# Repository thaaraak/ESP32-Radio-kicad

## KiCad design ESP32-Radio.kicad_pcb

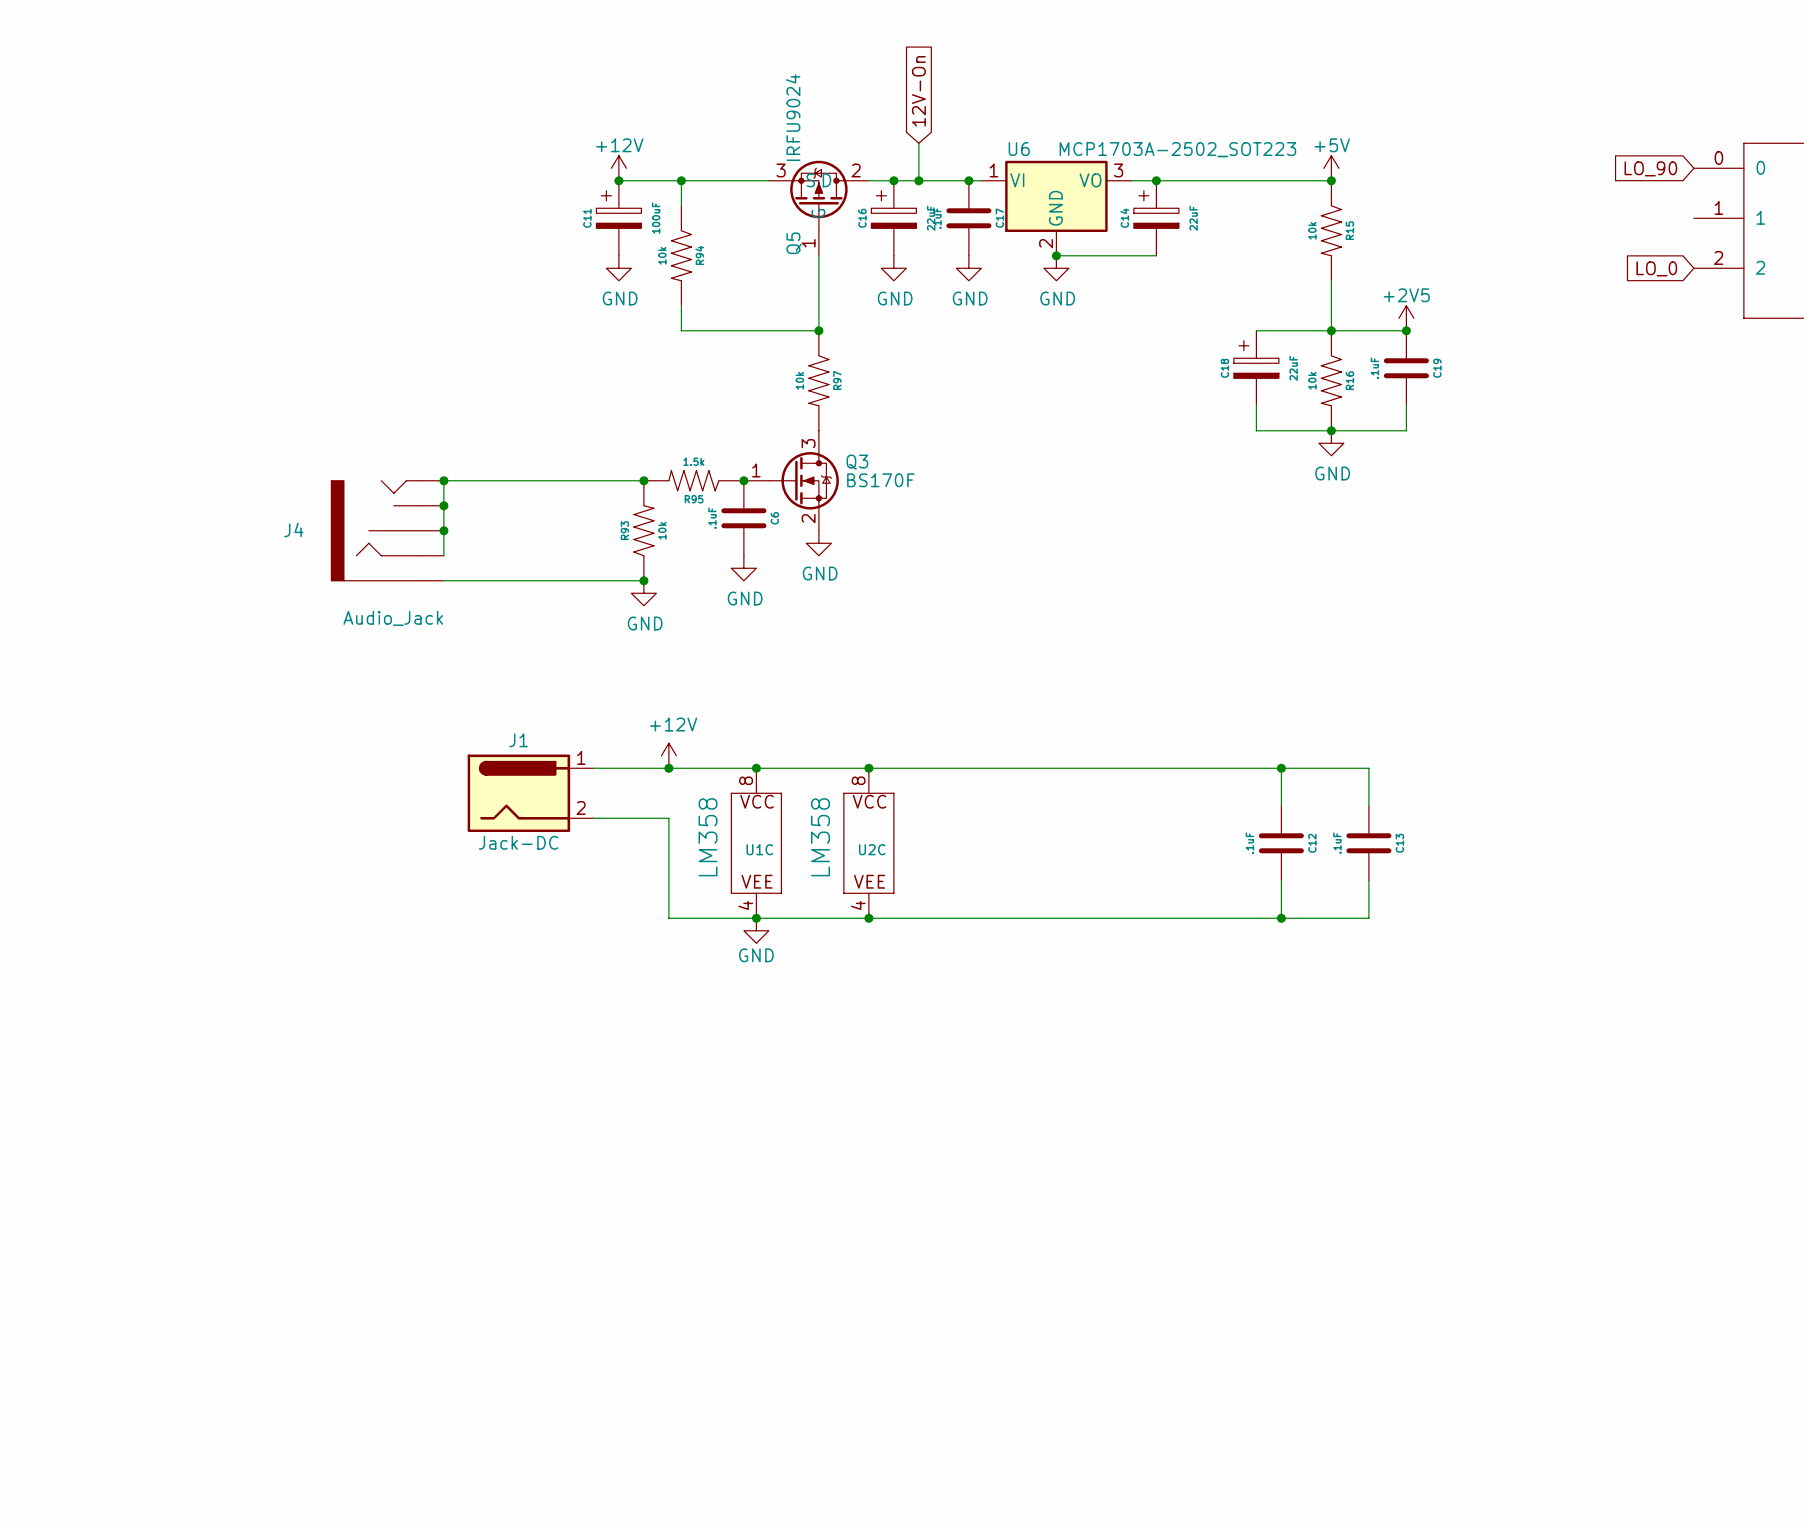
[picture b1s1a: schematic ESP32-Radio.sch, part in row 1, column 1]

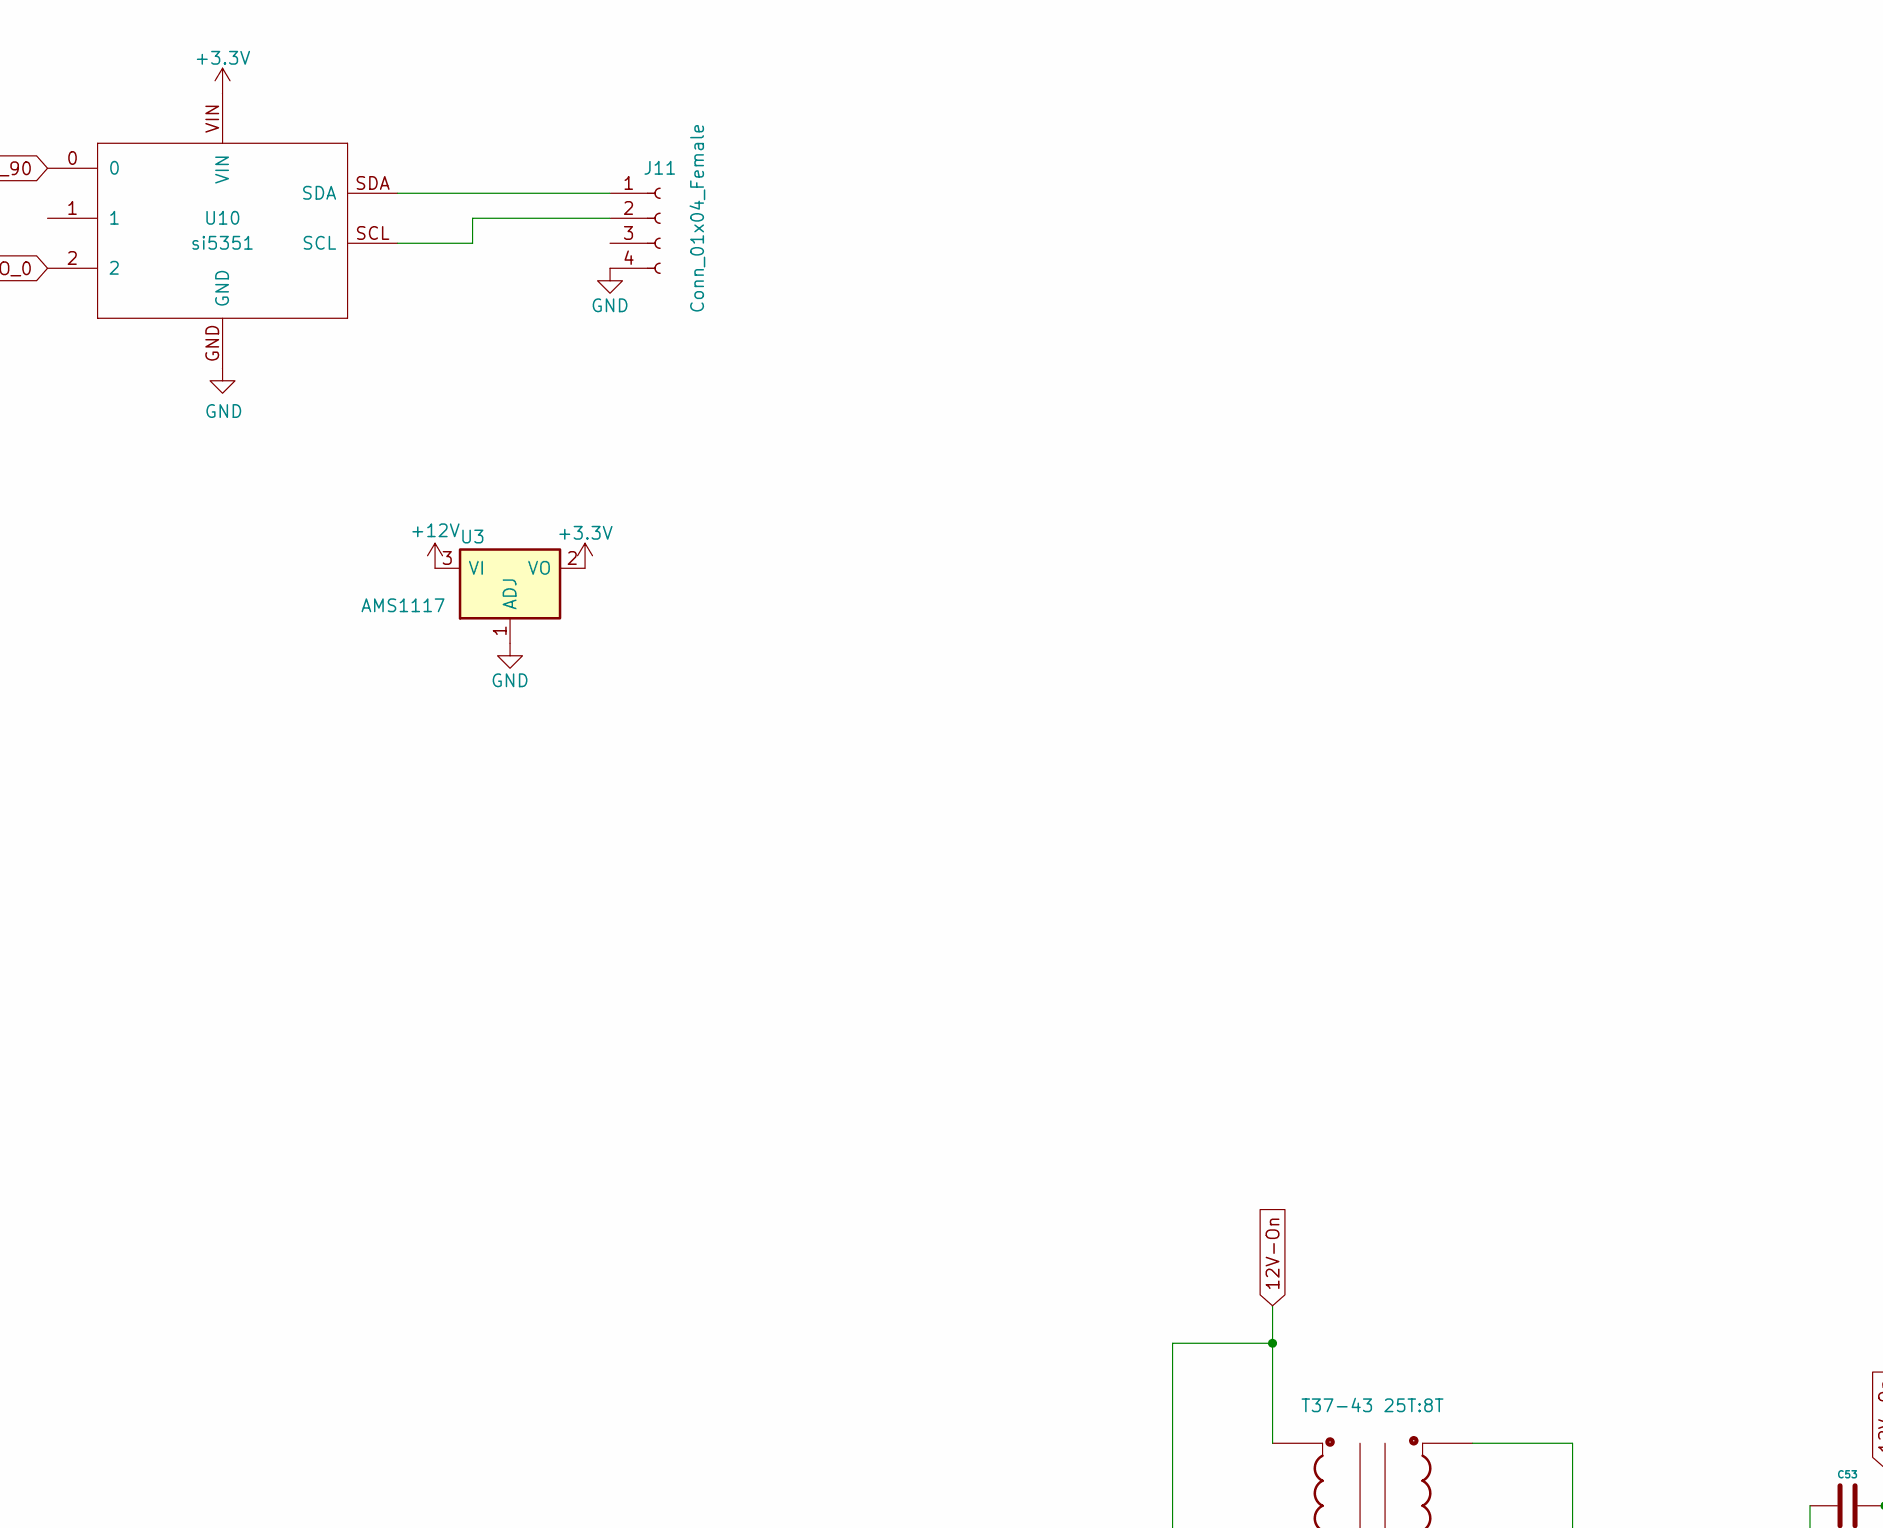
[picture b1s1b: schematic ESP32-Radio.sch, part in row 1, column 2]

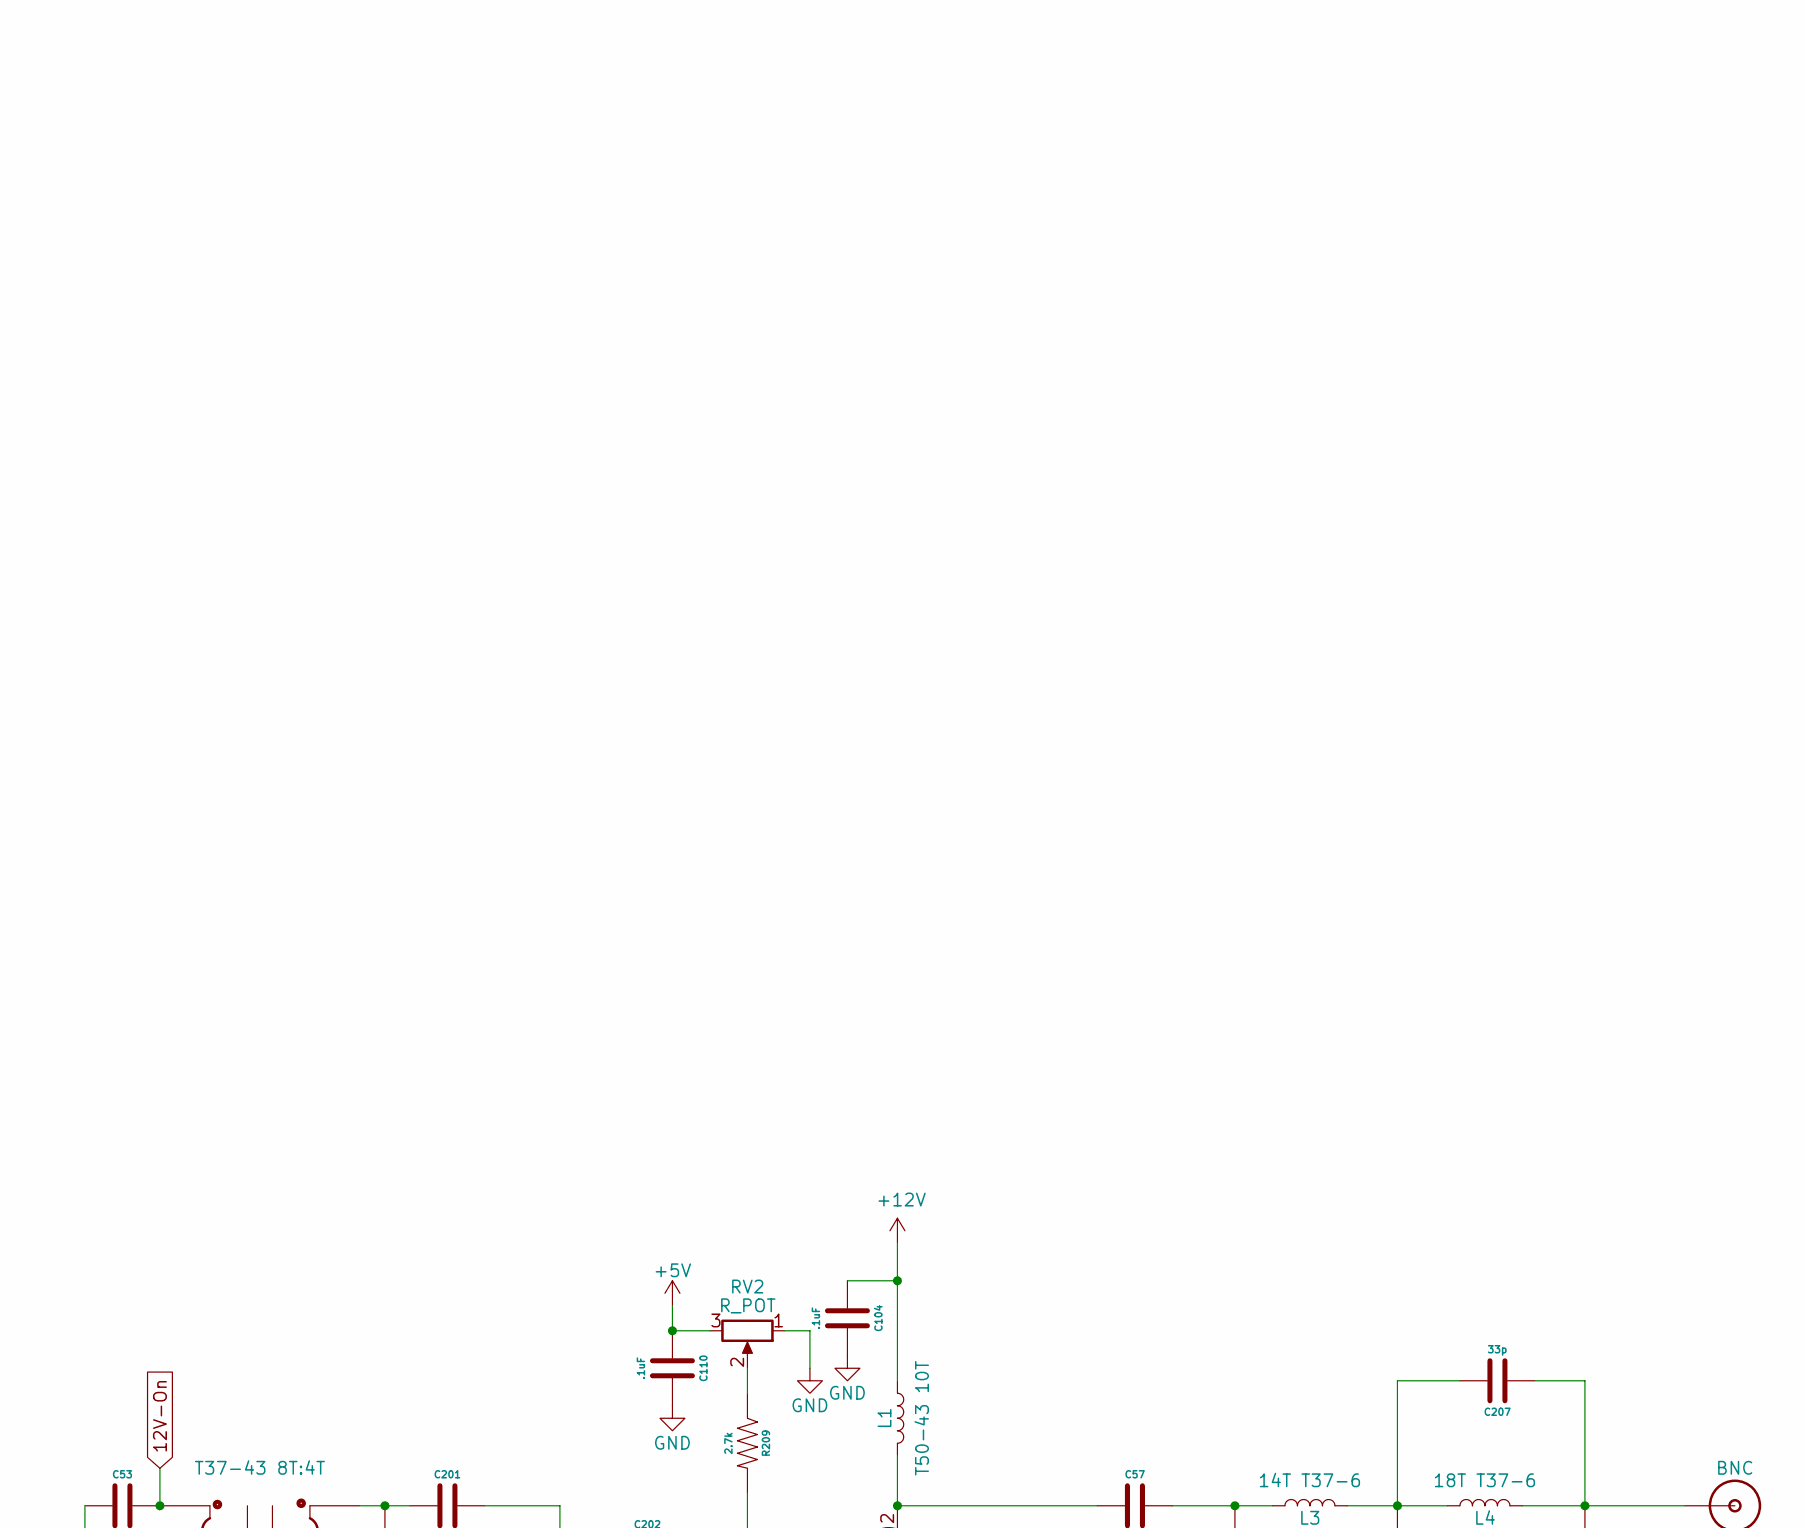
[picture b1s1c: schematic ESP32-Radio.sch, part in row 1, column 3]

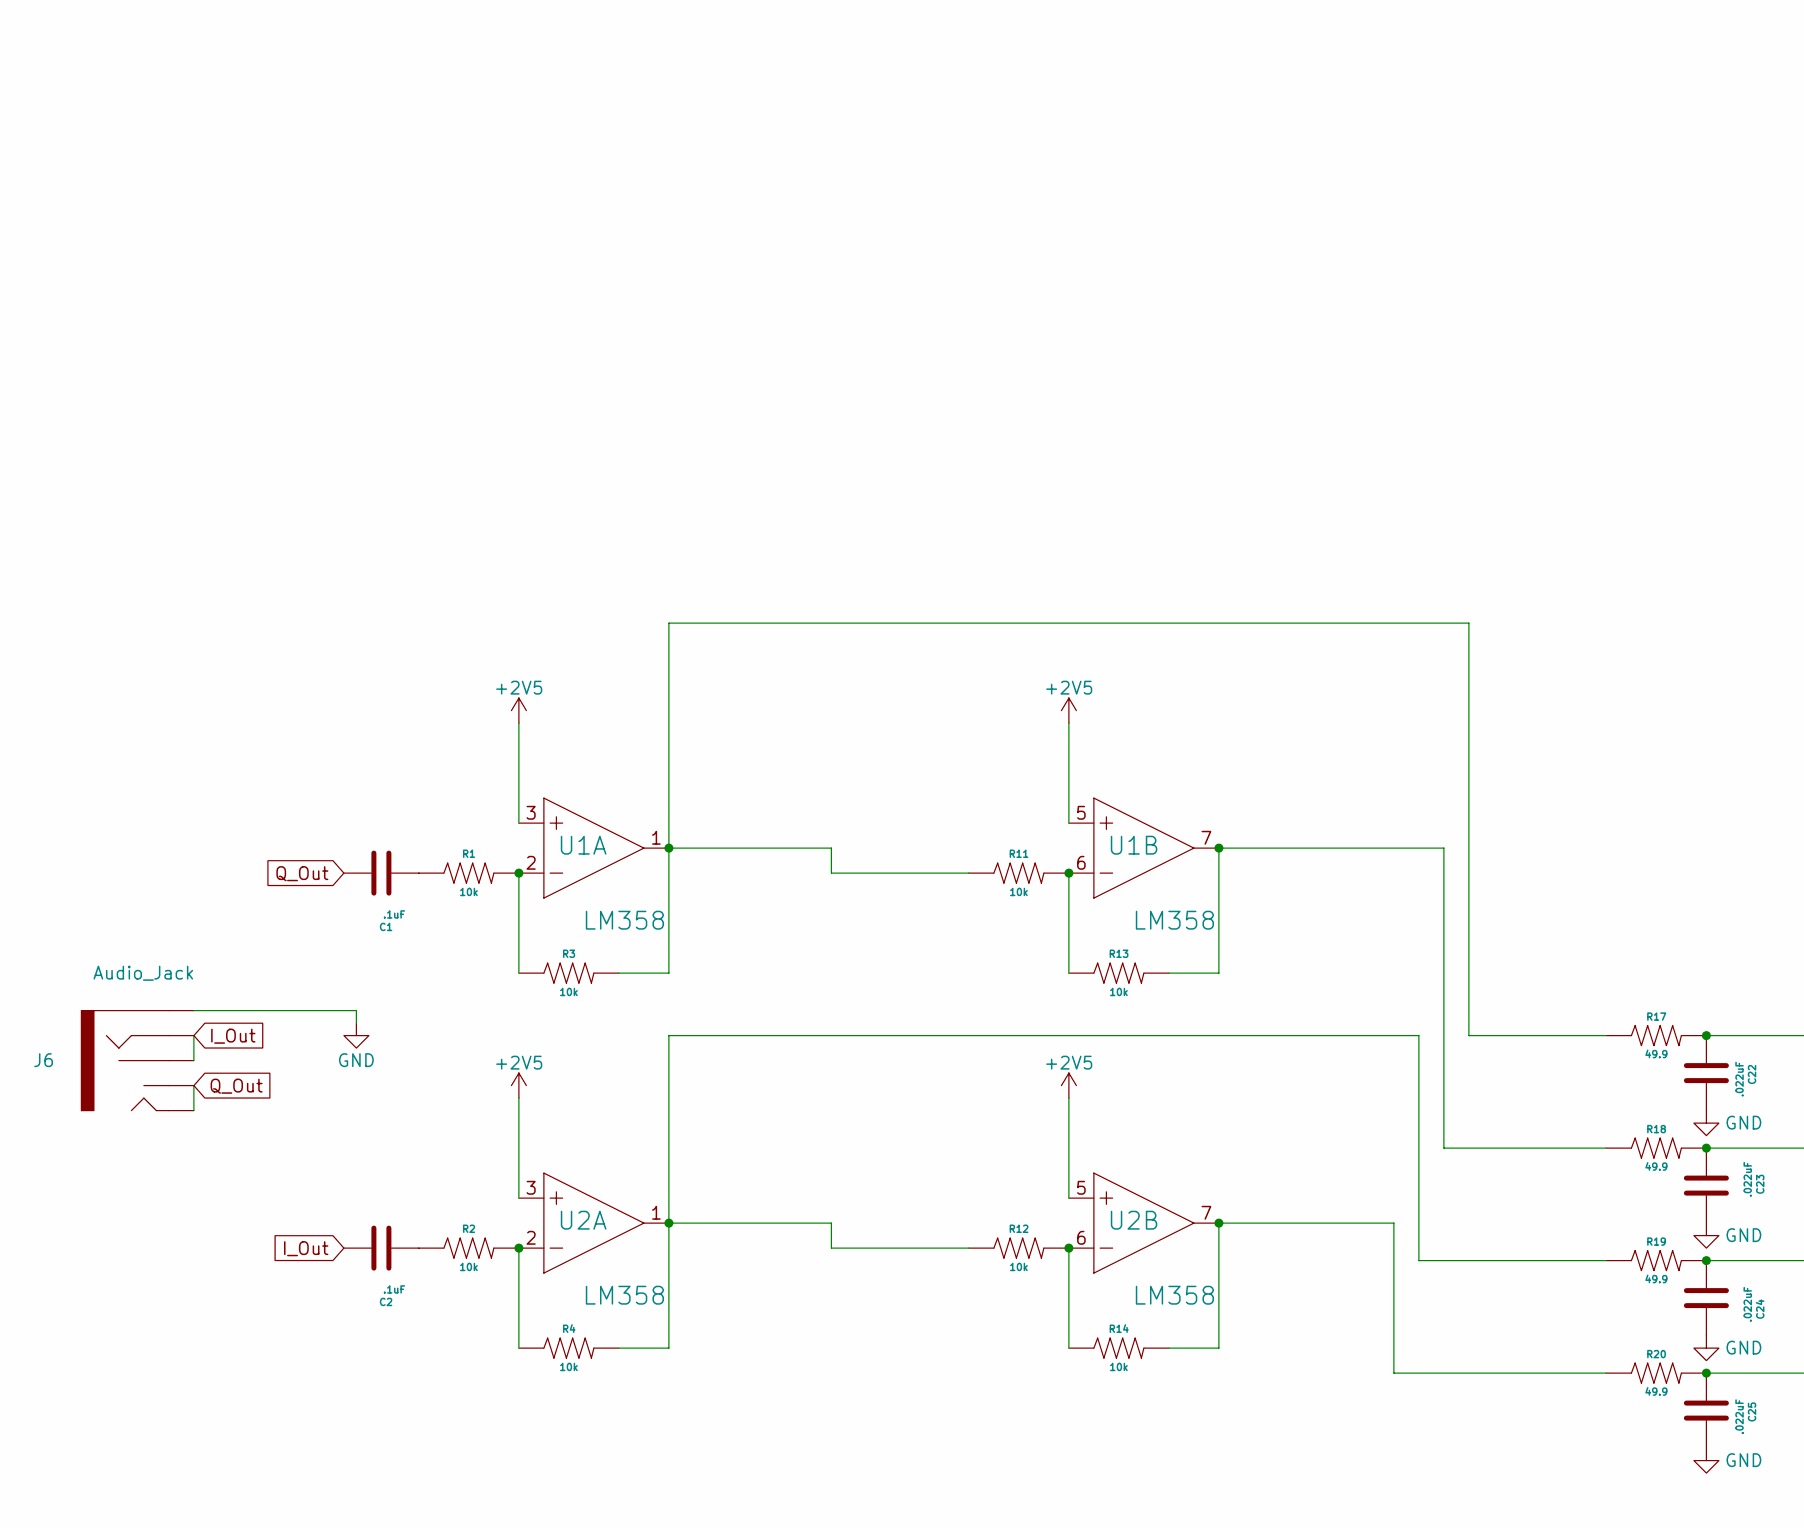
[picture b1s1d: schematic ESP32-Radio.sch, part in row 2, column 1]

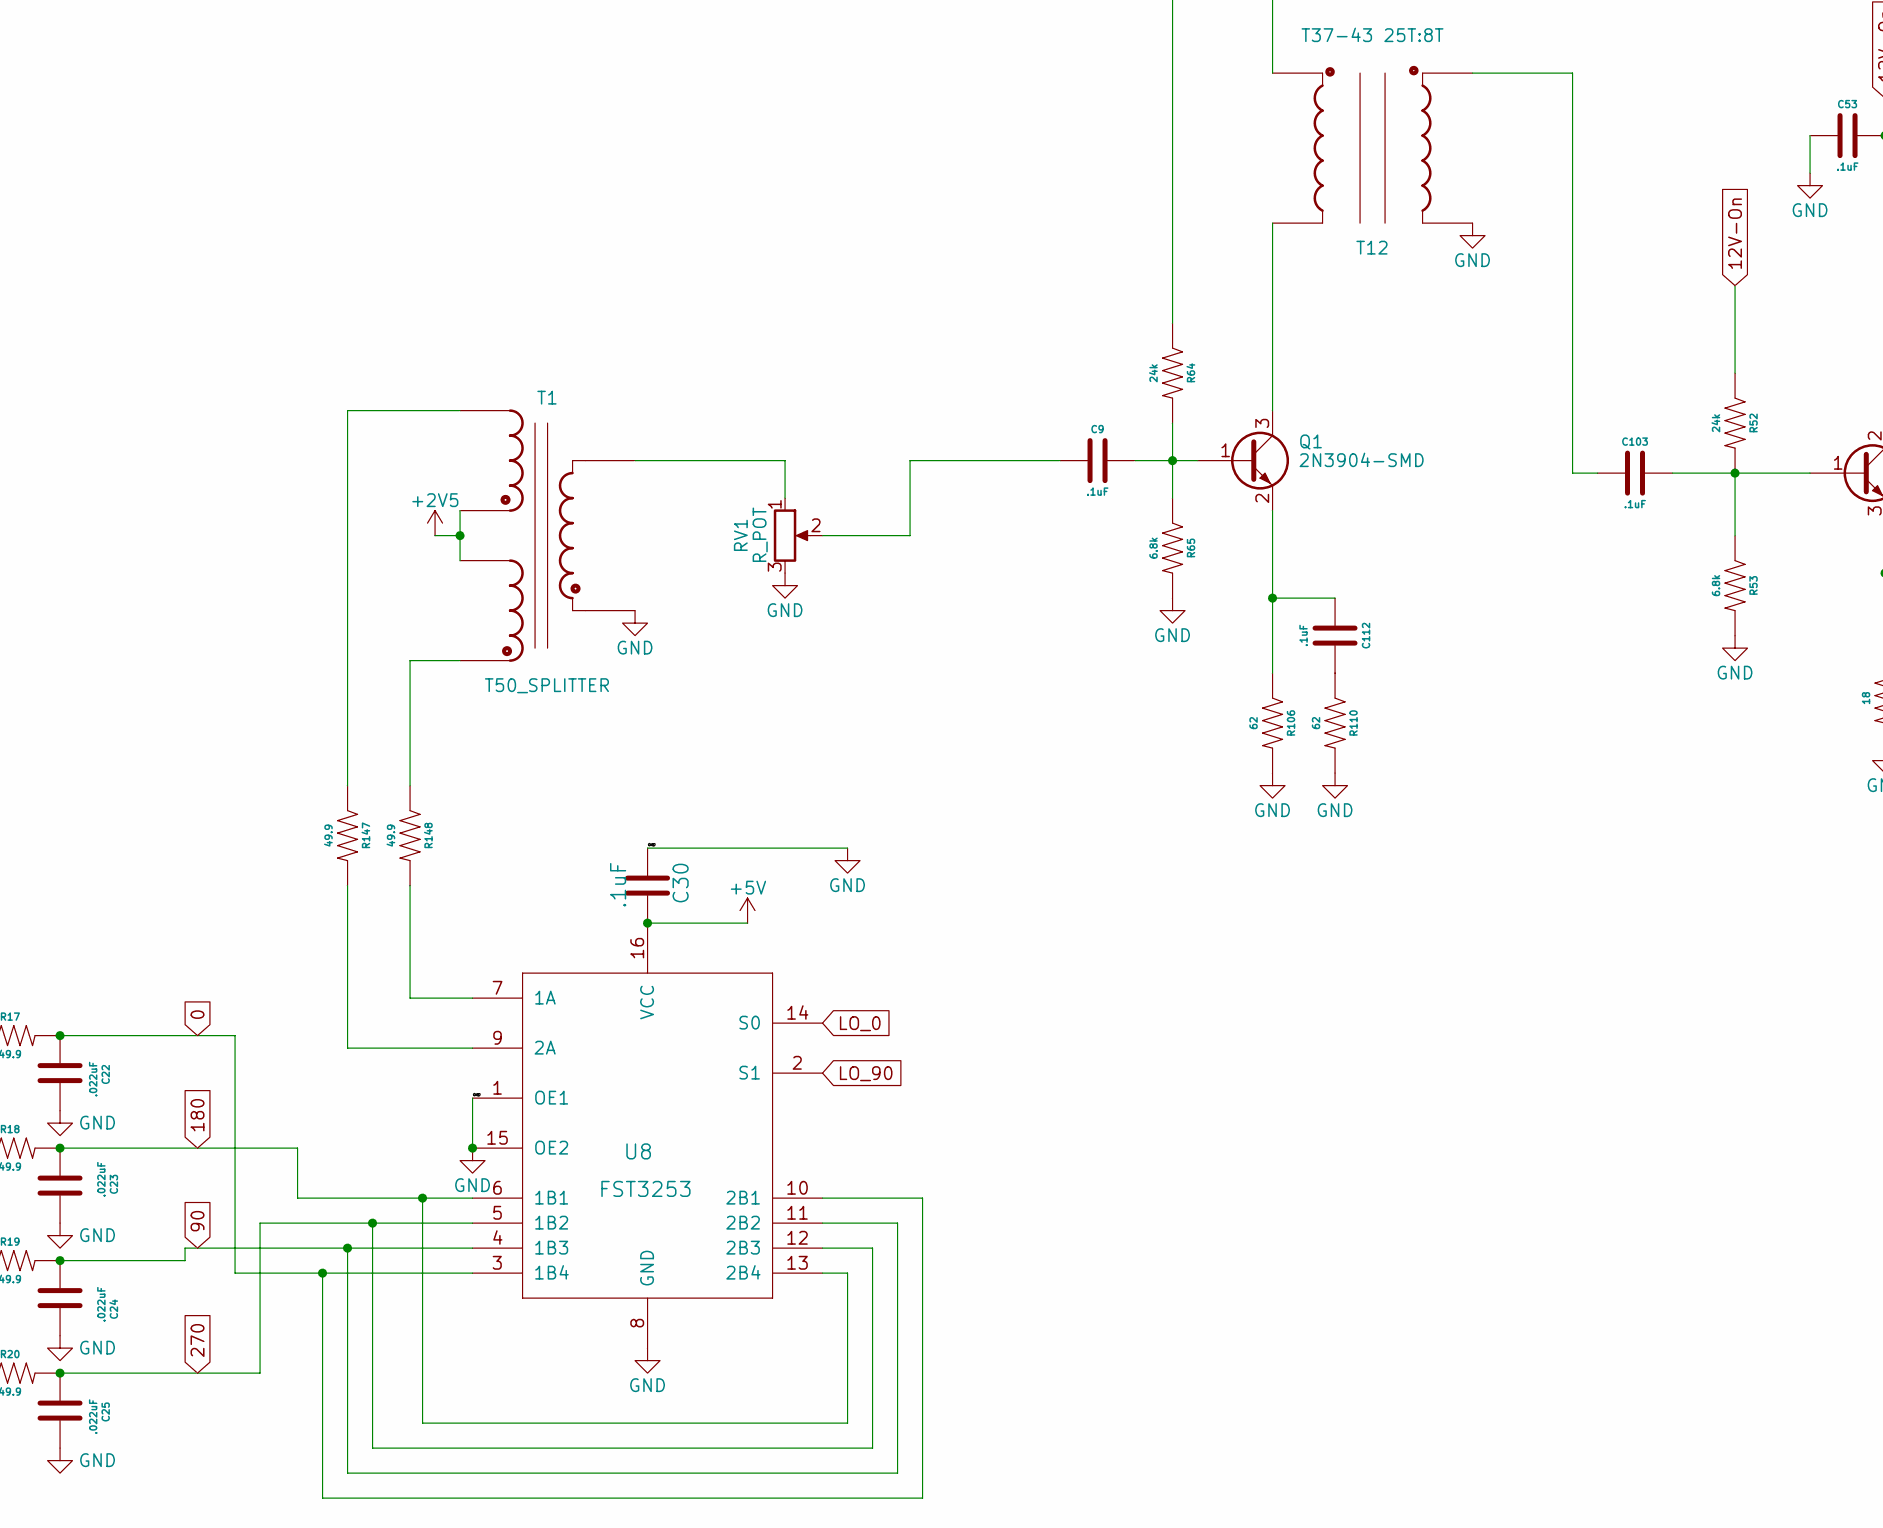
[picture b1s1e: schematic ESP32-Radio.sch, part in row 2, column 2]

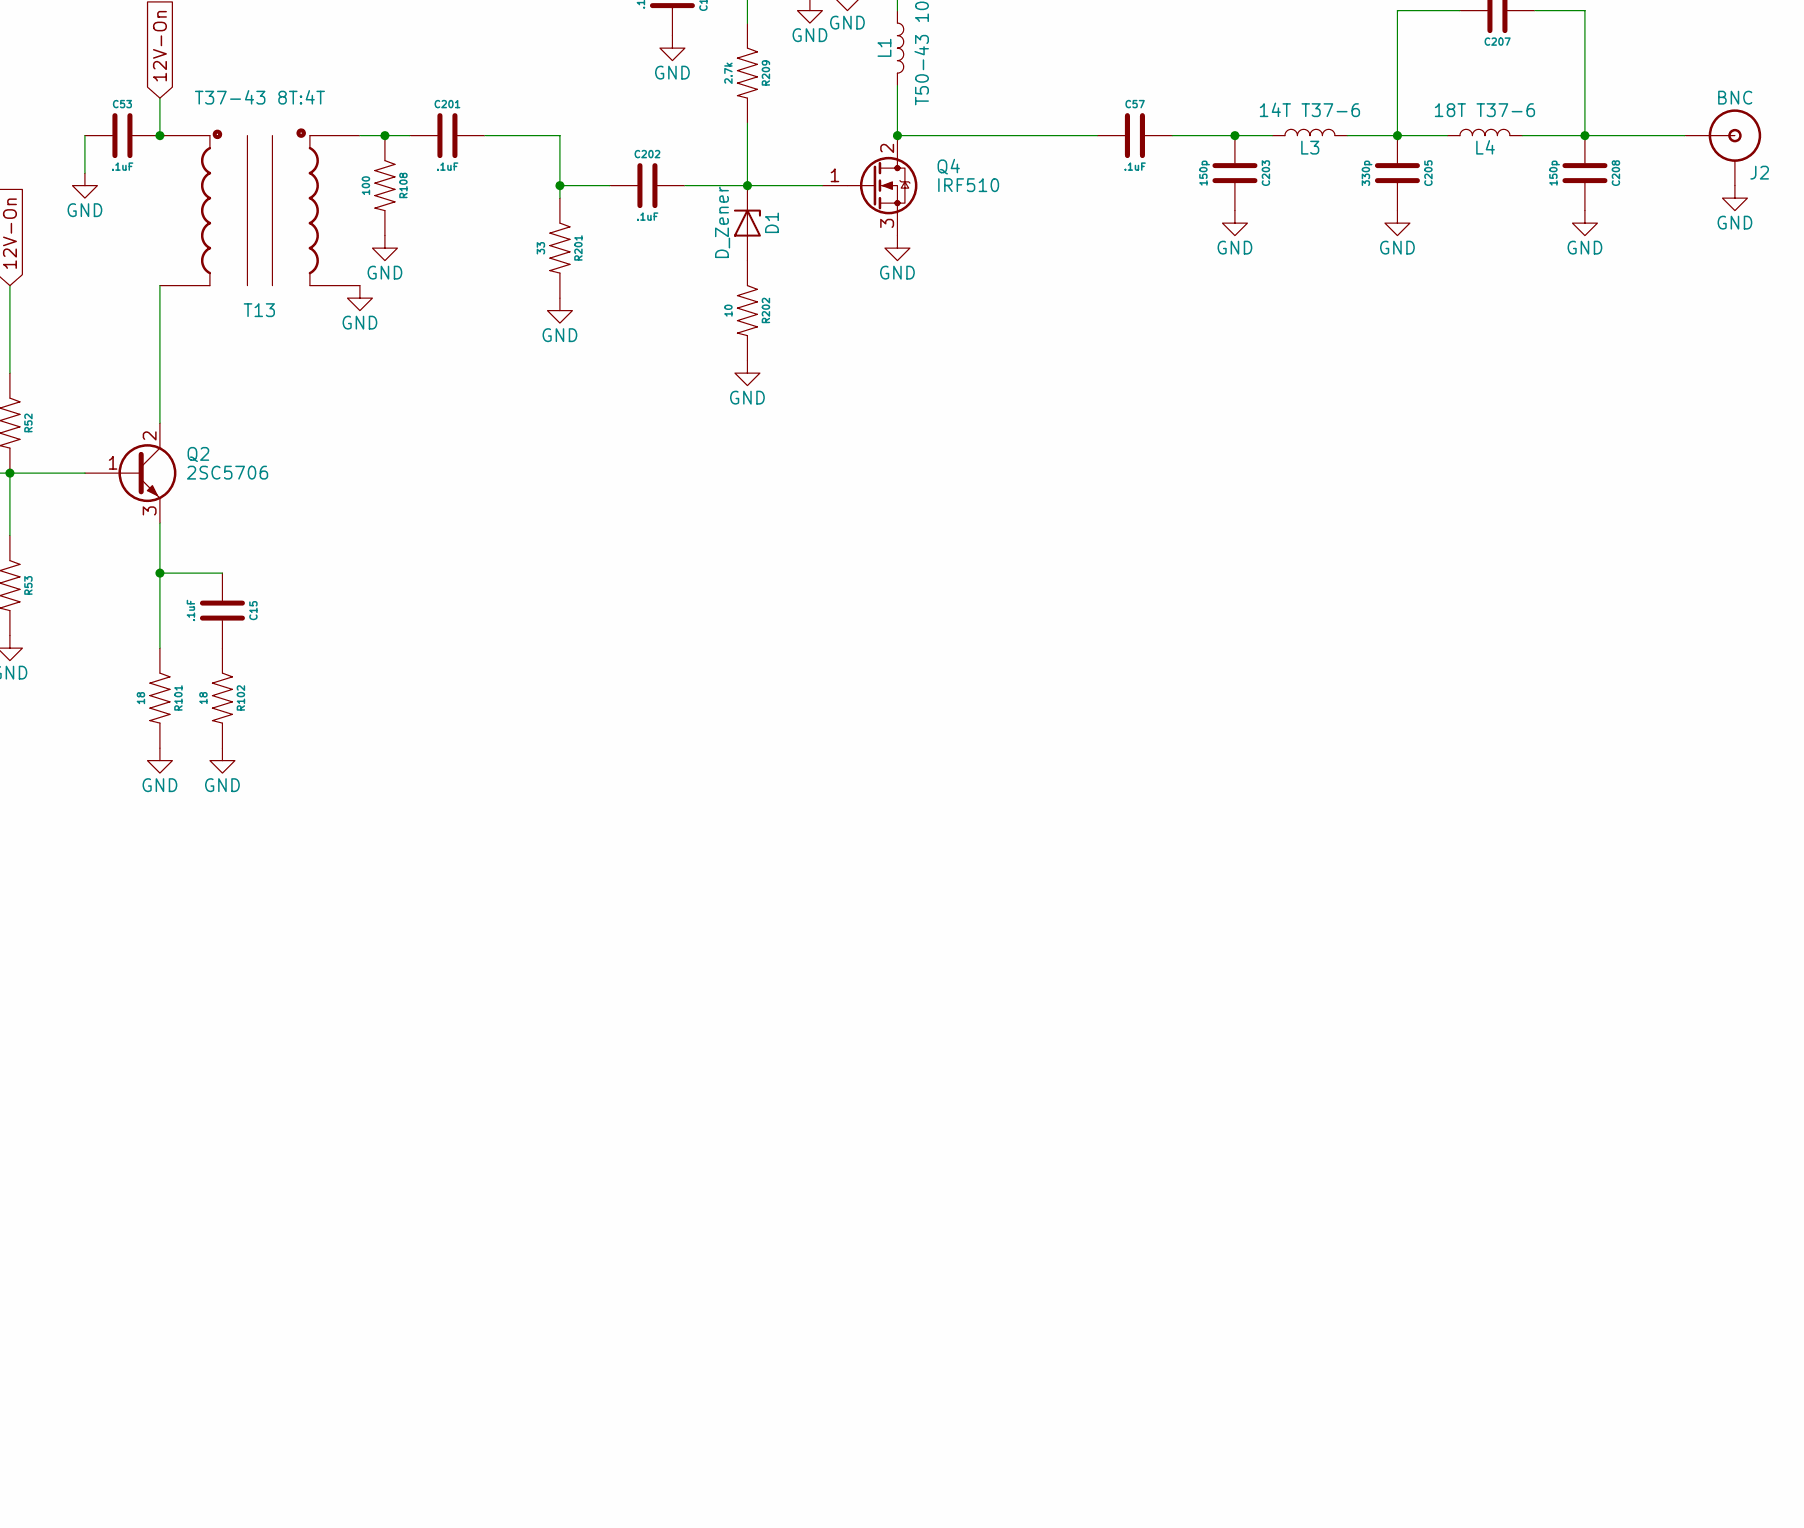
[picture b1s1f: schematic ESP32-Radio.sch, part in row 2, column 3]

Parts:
C1, C2, C6, C9, C12, C13, C15, C17, C19, C30, C53, C57, C103, C104, C110, C112, C201, C202: .1uF; Capacitor 0805
C11: 100uF; Cap_6.3x5.4
C14, C16, C18: 22uF; Cap_4x5.4
C22, C23, C24, C25: .022uF; Capacitor 1206
C203, C208: 150p; Capacitor 1206
C205: 330p; Capacitor 1206
C207: 33p; Capacitor 1206
D1: D_Zener; D_MiniMELF
J1: Jack-DC; BarrelJack_Horizontal
J2: BNC
J4, J6: Audio_Jack
J11: Conn_01x04_Female; PinHeader_1x04_P2.54mm_Vertical
L1: T50-43 10T; T50_Inductor
L3: 14T T37-6; T37_Inductor
L4: 18T T37-6; T37_Inductor
Q1: 2N3904-SMD; SOT-23
Q2: 2SC5706; TO-252-2
Q3: BS170F; SOT-23
Q4: IRF510; TO-220-3_Vertical
Q5: IRFU9024; TO-251-3_Vertical
R1, R2, R3, R4, R11, R12, R13, R14, R15, R16, R93, R94, R97: 10k; Resistor 0805
R17, R18, R19, R20, R147, R148: 49.9; Resistor 0805
R52, R64: 24k; Resistor 0805
R53, R65: 6.8k; Resistor 0805
R95: 1.5k; Resistor 0805
R101, R102: 18; Resistor 0805
R106, R110: 62; Resistor 0805
R108: 100; Resistor 0805
R201: 33; Resistor 0805
R202: 10; Resistor 0805
R209: 2.7k; Resistor 0805
RV1, RV2: R_POT; Trimpot Vertical
T1: T50_SPLITTER; T50 Trifilar
T12: T37-43 25T:8T; T37 Transformer
T13: T37-43 8T:4T; T37 Transformer
U1, U2: LM358; SO08
U3: AMS1117; SOT-223-3_TabPin2
U6: MCP1703A-2502_SOT223; TO-252-3_TabPin2
U8: FST3253; SO16
U10: si5351

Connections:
0: C22.2, R17.2, U8.3 (1B4), U8.10 (2B1)
12V-On: C16.1, C17.1, C53.1, Q5.2 (D), R52.1, R64.1, T12.C1B, T13.C1B, U6.1 (VI)
90: C24.1, R19.2, U8.4 (1B3), U8.11 (2B2)
180: C23.1, R18.2, U8.6 (1B1), U8.13 (2B4)
270: C25.2, R20.2, U8.5 (1B2), U8.12 (2B3)
+2V5: C18.1, C19.1, R15.2, R16.1, T1.C2A, T1.C3B, U1.3 (+IN), U1.5 (+IN), U2.3 (+IN), U2.5 (+IN)
+3V3: U3.2 (VO), U10.VIN
+5V: C14.1, C30.2, C110.1, R15.1, RV2.3, U6.3 (VO), U8.16 (VCC)
+12V: C11.1, C12.1, C13.1, C104.1, J1.1, L1.1, Q5.3 (S), R94.1, U1.8 (P$V+), U2.8 (P$V+), U3.3 (VI)
GND: C6.2, C11.2, C12.2, C13.2, C14.2, C16.2, C17.2, C18.2, C19.2, C22.1, C23.2, C24.2, C25.1, C30.1, C53.2, C104.2, C110.2, C203.2, C205.2, C208.2, J1.2, J2.GND, J4.SLEEVE, J6.SLEEVE, J11.4, Q3.2 (S), Q4.3 (S), R16.2, R53.2, R65.2, R93.1, R101.2, R102.2, R106.2, R108.2, R110.2, R201.2, R202.2, RV1.3, RV2.1, T1.C1B, T12.C2A, T13.C2A, U1.4 (P$V-), U2.4 (P$V-), U3.1 (ADJ), U6.2 (GND), U8.1 (OE1), U8.8 (GND), U8.15 (OE2), U10.GND
I_Out: C2.2, J6.RING, J6.RSH
LO_0: U8.14 (S0), U10.2
LO_90: U8.2 (S1), U10.0
unnamed: C1.1, R1.1
unnamed: C2.1, R2.1
unnamed: C6.1, Q3.1 (G), R95.1
unnamed: C9.1, RV1.2
unnamed: C9.2, Q1.1 (B), R64.2, R65.1
unnamed: C15.1, Q2.3 (E), R101.1
unnamed: C15.2, R102.1
unnamed: C57.1, L1.2, Q4.2 (D)
unnamed: C103.1, T12.C2B
unnamed: C103.2, Q2.1 (B), R52.2, R53.1
unnamed: C112.1, Q1.2 (E), R106.1
unnamed: C112.2, R110.1
unnamed: C201.1, R108.1, T13.C2B
unnamed: C201.2, C202.1, R201.1
unnamed: C202.2, D1.1 (K), Q4.1 (G), R209.2
unnamed: C57.2, C203.1, L3.1
unnamed: C205.1, C207.2, L3.2, L4.1
unnamed: C207.1, C208.1, J2.S (OUT), L4.2
unnamed: D1.2 (A), R202.1
unnamed: J4.RING, J4.RSH, J4.TIP, J4.TSH, R93.2, R95.2
unnamed: J11.1, U10.SDA
unnamed: J11.2, U10.SCL
unnamed: Q1.3 (C), T12.C1A
unnamed: Q2.2 (C), T13.C1A
unnamed: Q3.3 (D), R97.2
unnamed: Q5.1 (G), R94.2, R97.1
unnamed: R1.2, R3.1, U1.2 (-IN)
unnamed: R2.2, R4.1, U2.2 (-IN)
unnamed: R3.2, R11.1, R17.1, U1.1 (OUT)
unnamed: R11.2, R13.1, U1.6 (-IN)
unnamed: R4.2, R12.1, R19.1, U2.1 (OUT)
unnamed: R12.2, R14.1, U2.6 (-IN)
unnamed: R13.2, R18.1, U1.7 (OUT)
unnamed: R14.2, R20.1, U2.7 (OUT)
unnamed: R147.1, T1.C3A
unnamed: R147.2, U8.9 (2A)
unnamed: R148.1, T1.C2B
unnamed: R148.2, U8.7 (1A)
unnamed: R209.1, RV2.2
unnamed: RV1.1, T1.C1A
Q_Out: C1.2, J6.TIP, J6.TSH

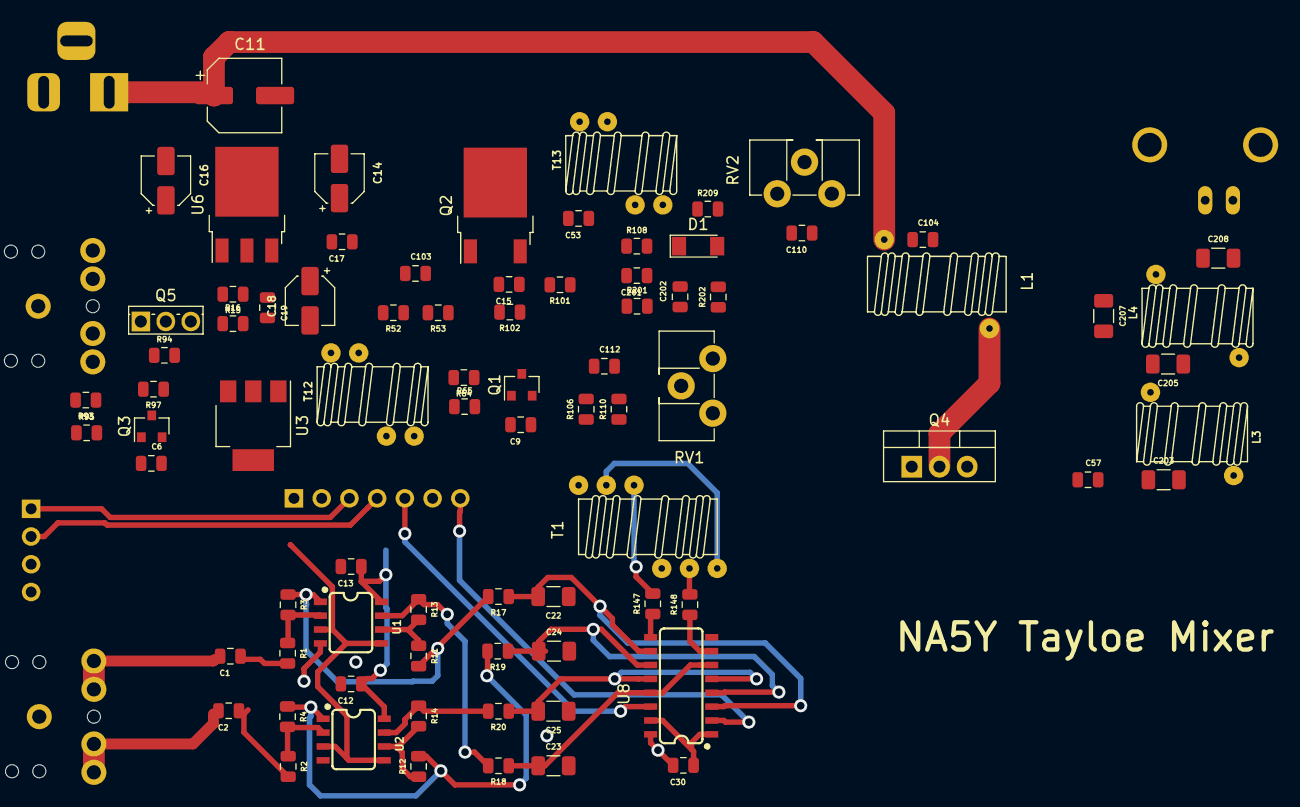
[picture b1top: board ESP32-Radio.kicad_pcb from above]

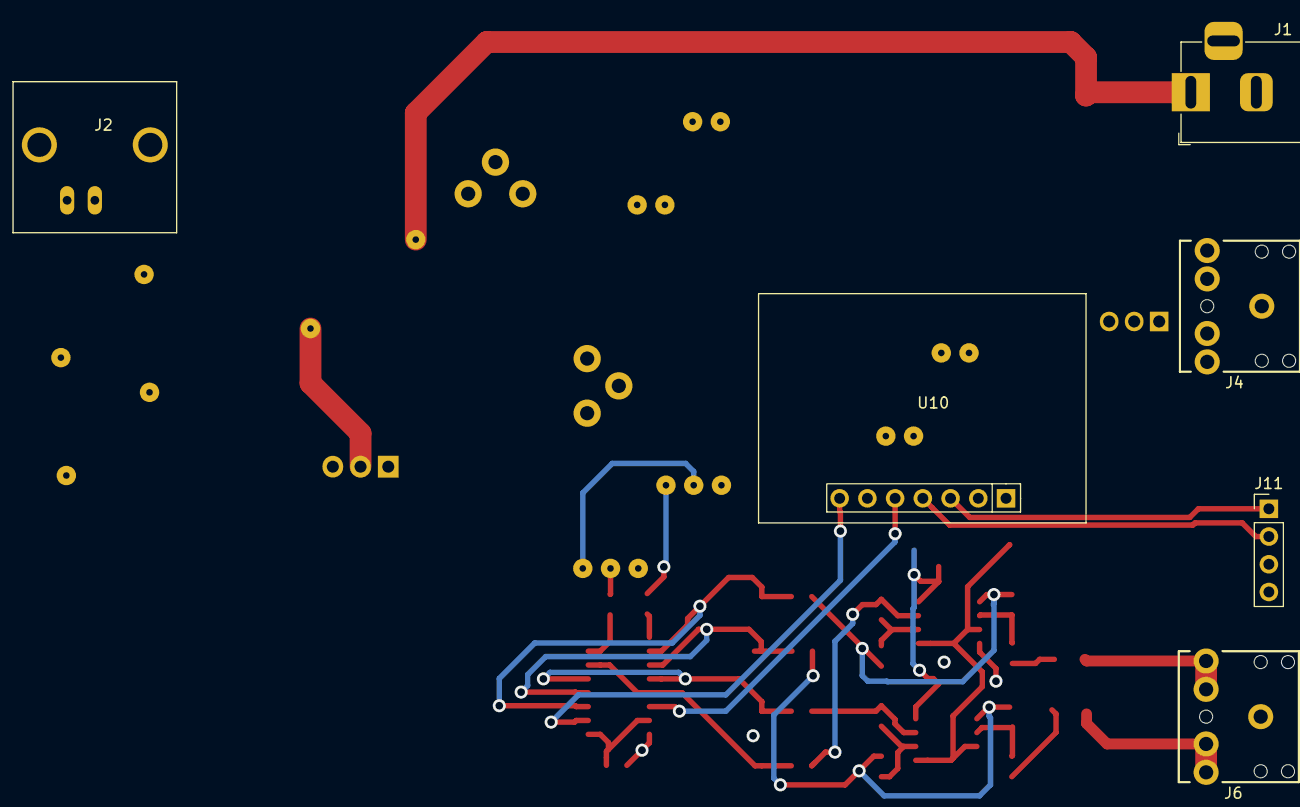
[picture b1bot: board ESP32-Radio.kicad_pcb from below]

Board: 2 copper layers, 87 parts (6 on the bottom side), 54 nets.

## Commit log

2021-07-01 First
2021-07-01 fixed references
2021-07-01 more fixes
2021-07-02 added gitignore
2021-07-10 added pa
2021-07-13 added emiiter smd resistor
2021-07-13 fixed gnd
2021-07-13 added trap to lowpass
2021-07-15 fixed rescue reference
2021-08-22 created
2021-08-22 added separate 2.5v to combiner
